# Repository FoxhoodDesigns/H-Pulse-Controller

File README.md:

# H-Pulse Train controller (G4)
A advanced Electronic Speed Control intended for controlling Model trains. Though the load is simple, this ESC is equipped with the means to enable advanced monitoring/control of model trains
In the long-run the controller can be programmed to be able to communicate to digital trains via Digital-Command-Control (DCC)

# Specifications:
+ INPUT:	8-24V DC
+ OUTPUT: 8-24V <6A
+ TDP: ~1-5 Watt depending on load
+ Controller: Raspberry Pi RP2040 125Mhz Dual-core ARM microcontroller.
+ Driver: Infineon TLE9201 6A H-Bridge motor driver with SPI interface
+ Display: GC9A01 240x240 circular IPS Monitor

# Features:
+ Current Monitoring
+ Voltage Monitoring
+ Reverse Polarity Protection
+ Transient Voltage Suppression
+ Overcurrent Detection / Short-circuit protection
+ Under-voltage lockout
+ Open-load (Derail) detection
+ FAN Load switch
+ Piezo-speaker for feedback
+ Extra headers for (Matrix) IO
+ DCC-Ready Hardware

# Current Status:
Testing IO Expansion part on a breadboard. Creating initial firmware and drawing the Icons that are to be displayed on the GC9A01.

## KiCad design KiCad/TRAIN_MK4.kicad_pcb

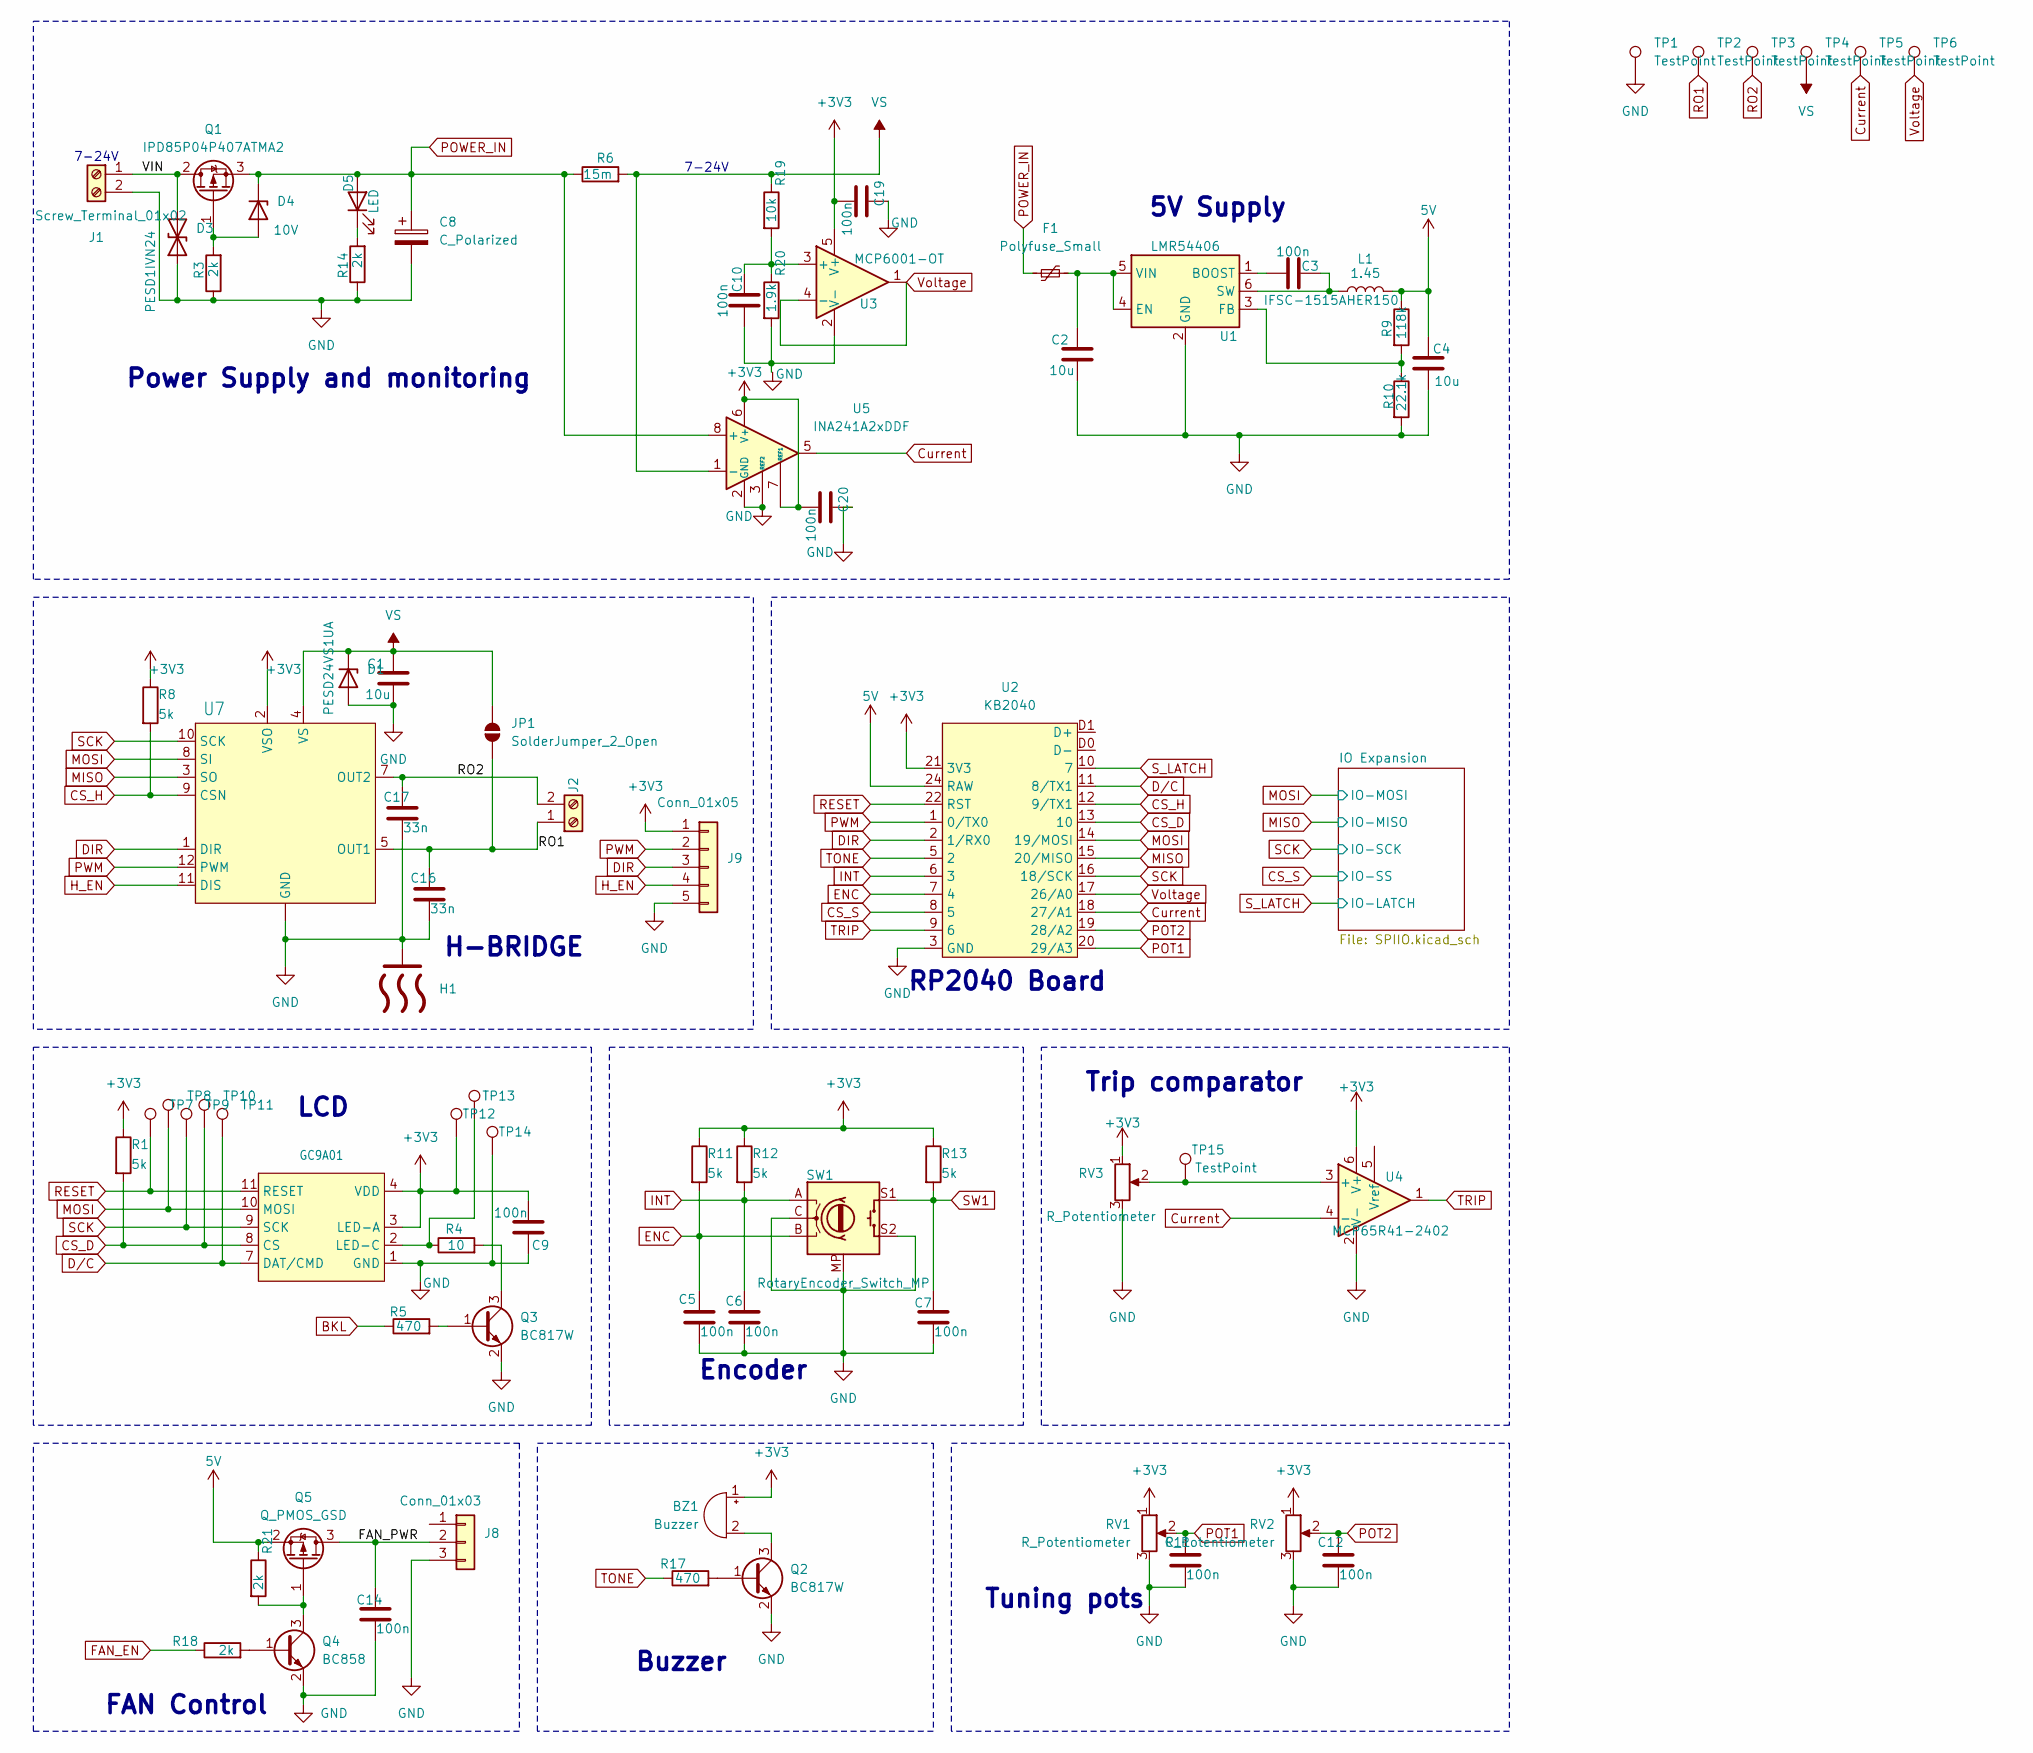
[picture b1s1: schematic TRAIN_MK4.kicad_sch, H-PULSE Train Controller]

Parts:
BZ1: Buzzer; PUIAudio_SMT_0825_S_4_R
C1, C2, C4: 10u; C_1210_3225Metric_Pad1.33x2.70mm_HandSolder
C3, C5, C6, C7, C9, C10, C11, C12, C14, C19, C20: 100n; C_0805_2012Metric_Pad1.18x1.45mm_HandSolder; Voltage 1kV; Tolerance 100%
C8: C_Polarized; CP_Elec_10x10
C16, C17: 33n; C_0805_2012Metric_Pad1.18x1.45mm_HandSolder; Voltage 1kV; Tolerance 100%
D1: PESD24VS1UA; D_SOD-323_HandSoldering
D3: PESD1IVN24; D_SOD-323_HandSoldering
D4: 10V; Nexperia_CFP3_SOD-123W
D5: LED; LED_0805_2012Metric_Pad1.15x1.40mm_HandSolder
F1: Polyfuse_Small; Fuse_1812_4532Metric_Pad1.30x3.40mm_HandSolder
H1: DPAK-Heatsink
J1, J2: Screw_Terminal_01x02; TerminalBlock_Phoenix_PT-1,5-2-5.0-H_1x02_P5.00mm_Horizontal
J8: Conn_01x03; FanPinHeader_1x03_P2.54mm_Vertical
J9: Conn_01x05; PinHeader_1x05_P2.54mm_Vertical
JP1: SolderJumper_2_Open; SolderJumper-2_P1.3mm_Open_Pad1.0x1.5mm
L1: IFSC-1515AHER150; L_Vishay_IFSC-1515AH_4x4x1.8mm
Q1: IPD85P04P407ATMA2; TO-252-2
Q2, Q3: BC817W; SOT-323_SC-70
Q4: BC858; SOT-323_SC-70_Handsoldering
Q5: Q_PMOS_GSD; SOT-23
R1, R8, R11, R12, R13: 5k; R_0805_2012Metric_Pad1.20x1.40mm_HandSolder
R3, R14, R18, R21: 2k; R_0805_2012Metric_Pad1.20x1.40mm_HandSolder
R4: 10; R_0805_2012Metric_Pad1.20x1.40mm_HandSolder
R5, R17: 470; R_0805_2012Metric_Pad1.20x1.40mm_HandSolder
R6: 15m; R_2010_5025Metric_Pad1.40x2.65mm_HandSolder
R9: 118k; R_0805_2012Metric_Pad1.20x1.40mm_HandSolder
R10: 22.1k; R_0805_2012Metric_Pad1.20x1.40mm_HandSolder
R19: 10k; R_0805_2012Metric_Pad1.20x1.40mm_HandSolder
R20: 1.9k; R_0805_2012Metric_Pad1.20x1.40mm_HandSolder
RV1, RV2: R_Potentiometer; Potentiometer_Vishay_T73YP_Vertical
RV3: R_Potentiometer; Potentiometer_Bourns_3214X_Vertical
SW1: RotaryEncoder_Switch_MP; RotaryEncoder_Bourns_Vertical_PEC12R-3x17F-Sxxxx
TP1, TP2, TP3, TP4, TP5, TP6: TestPoint; TestPoint_Pad_2.0x2.0mm
TP7, TP8, TP9, TP10, TP11, TP12, TP13, TP14: TestPoint; TestPoint_Pad_D1.0mm
TP15: TestPoint; TestPoint_Pad_D2.0mm
U1: LMR54406; TSOT-23-6
U2: KB2040
U3: MCP6001-OT; SOT-23-5
U4: MCP65R41-2402; SOT-23-6
U5: INA241A2xDDF; SOT-23-8
U7: Infineon_PG-DSO-12-17
U8: GC9A01; GC9A01INT

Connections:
5V: C4.1, L1.2, Q5.2 (S), R9.1, R21.1, U2.24 (RAW)
+3V3: BZ1.1 (+), C9.2, C19.2, C20.2, J9.1, R1.1, R8.1, R11.1, R12.1, R13.1, RV1.1, RV2.1, RV3.1, TP12.1, U2.21 (3V3), U3.5 (V+), U4.6 (V+), U5.6 (V+), U5.7 (REF1), U7.2 (VSO), U8.3 (LED-A), U8.4 (VDD); also elsewhere on the board
/FAN_PWR: C14.1, J8.2, Q5.3 (D)
/VIN: D3.2 (A2), J1.1, Q1.2 (D)
BKL: R5.1; also elsewhere on the board
CS_D: R1.2, TP10.1, U2.13 (10), U8.8 (CS)
CS_H: R8.2, U2.12 (9/TX1), U7.9 (CSN)
CS_S: U2.8 (5); also elsewhere on the board
Current: TP5.1, U2.18 (27/A1), U4.4 (-), U5.5
DIR: J9.3, U2.2 (1/RX0), U7.1 (DIR)
D/C: TP11.1, U2.11 (8/TX1), U8.7 (DAT/CMD)
ENC: C5.1, R11.2, SW1.B, U2.7 (4)
FAN_EN: R18.1; also elsewhere on the board
GND: C1.2, C2.2, C4.2, C5.2, C6.2, C7.2, C8.2, C9.1, C11.2, C12.2, C14.2, C16.2, C17.2, C19.1, C20.1, D1.2 (A), D3.1 (A1), H1.1, J1.2, J8.3, J9.5, Q2.2 (E), Q3.2 (E), Q4.2 (E), R3.1, R10.2, R14.1, RV1.3, RV2.3, RV3.3, SW1.C, SW1.MP, SW1.S2, TP1.1, TP14.1, U1.2 (GND), U2.3 (GND), U2.4 (GND), U2.23 (GND), U4.2 (V-), U5.2 (GND), U5.3 (REF2), U5.4 (GND), U7.6 (GND), U7.13 (GND), U8.1 (GND), U8.5 (GND), U8.6 (GND), U8.12 (GND); also elsewhere on the board
H_EN: J9.4, U7.11 (DIS); also elsewhere on the board
INT: C6.1, R12.2, SW1.A, U2.6 (3)
MISO: U2.15 (20/MISO), U7.3 (SO); also elsewhere on the board
MOSI: TP8.1, U2.14 (19/MOSI), U7.8 (SI), U8.10 (MOSI); also elsewhere on the board
unnamed: BZ1.2 (-), Q2.3 (C)
unnamed: D4.2 (A), Q1.1 (G), R3.2
unnamed: D5.1 (K), R14.2
unnamed: Q2.1 (B), R17.2
unnamed: Q3.1 (B), R5.2
unnamed: Q3.3 (C), R4.2
unnamed: Q4.1 (B), R18.2
unnamed: Q4.3 (C), Q5.1 (G), R21.2
unnamed: C3.2, U1.1 (BOOST)
unnamed: C2.1, F1.2, U1.4 (EN), U1.5 (VIN)
unnamed: R9.2, R10.1, U1.3 (FB)
unnamed: C3.1, L1.1, U1.6 (SW)
unnamed: C10.1, R19.2, R20.1, U3.3 (+)
unnamed: C10.2, R20.2, U3.2 (V-)
unnamed: RV3.2, TP15.1, U4.3 (+)
unnamed: R4.1, TP13.1, U8.2 (LED-C)
POT1: C11.1, RV1.2, U2.20 (29/A3)
POT2: C12.1, RV2.2, U2.19 (28/A2)
POWER_IN: C8.1, D4.1 (K), D5.2 (A), F1.1, Q1.3 (S), R6.1, U5.8 (+)
PWM: J9.2, U2.1 (0/TX0), U7.12 (PWM)
RESET: TP7.1, U2.22 (RST), U8.11 (RESET)
RO1: C16.1, J2.1, JP1.1 (A), TP2.1, U7.5 (OUT1)
RO2: C17.1, J2.2, TP3.1, U7.7 (OUT2)
SCK: TP9.1, U2.16 (18/SCK), U7.10 (SCK), U8.9 (SCK); also elsewhere on the board
SW1: C7.1, R13.2, SW1.S1; also elsewhere on the board
S_LATCH: U2.10 (7); also elsewhere on the board
TONE: R17.1, U2.5 (2)
TRIP: U2.9 (6), U4.1
VS: C1.1, D1.1 (K), JP1.2 (B), R6.2, R19.1, TP4.1, U5.1 (-), U7.4 (VS)
Voltage: TP6.1, U2.17 (26/A0), U3.1, U3.4 (-)

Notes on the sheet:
H-BRIDGE
Tuning pots
LCD
7-24V
Buzzer
RP2040 Board
5V Supply
FAN Control
Power Supply and monitoring
Trip comparator
Encoder

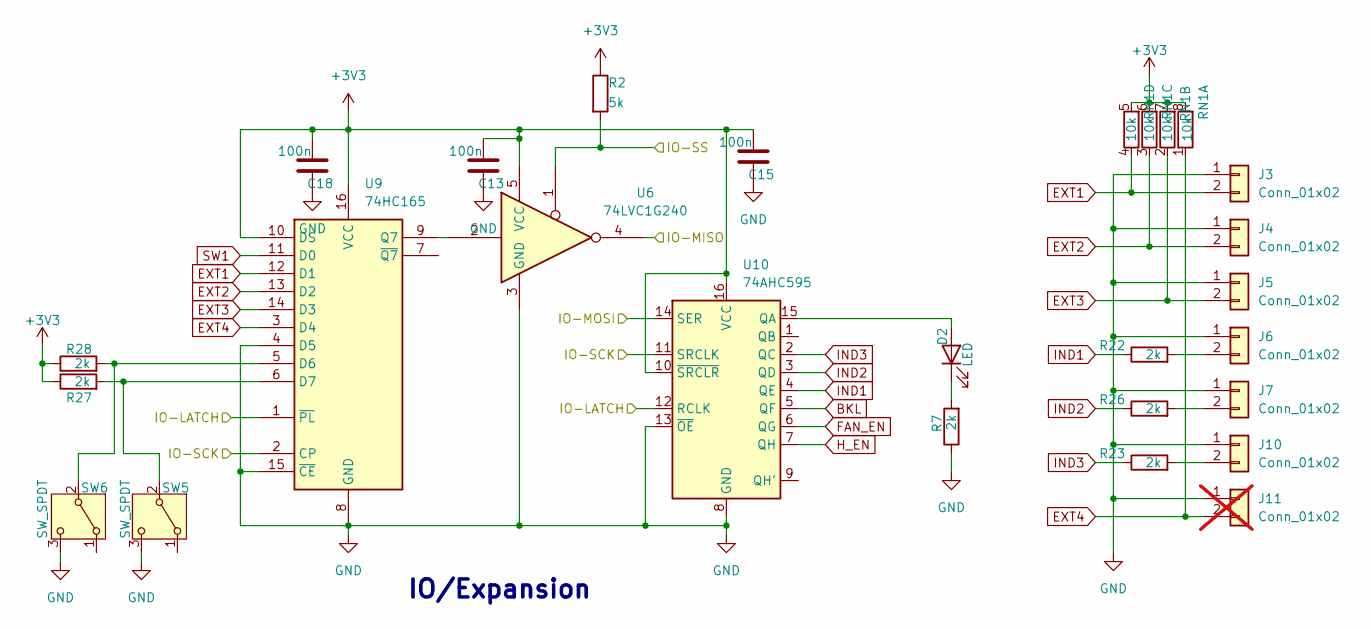
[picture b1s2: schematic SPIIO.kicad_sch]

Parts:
C13, C15, C18: 100n; C_0805_2012Metric_Pad1.18x1.45mm_HandSolder; Voltage 1kV; Tolerance 100%
D2: LED; LED_0805_2012Metric_Pad1.15x1.40mm_HandSolder
J3, J4, J5, J6, J7, J10: Conn_01x02; JST_XH_B2B-XH-A_1x02_P2.50mm_Vertical
J11: Conn_01x02; PinHeader_1x02_P2.54mm_Vertical_SMD_Pin1Right; not fitted
R2: 5k; R_0805_2012Metric_Pad1.20x1.40mm_HandSolder
R7, R22, R23, R26, R27, R28: 2k; R_0805_2012Metric_Pad1.20x1.40mm_HandSolder
RN1: 10k; R_Array_Convex_4x0603
SW5, SW6: SW_SPDT; SW_Slide_SPDT_Straight_CK_OS102011MS2Q
U6: 74LVC1G240; SOT-23-5_HandSoldering
U9: 74HC165; TSSOP-16_4.4x5mm_P0.65mm
U10: 74AHC595; TSSOP-16_4.4x5mm_P0.65mm

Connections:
+3V3: C13.2, C15.2, C18.2, R2.1, R27.1, R28.1, RN1.5 (R4.2), RN1.6 (R3.2), RN1.7 (R2.2), RN1.8 (R1.2), U6.5 (VCC), U9.10 (DS), U9.16 (VCC), U10.10 (~SRCLR), U10.16 (VCC); also elsewhere on the board
BKL: U10.5 (QF); also elsewhere on the board
CS_S: R2.2, U6.1; also elsewhere on the board
EXT1: J3.2, RN1.4 (R4.1), U9.12 (D1)
EXT2: J4.2, RN1.3 (R3.1), U9.13 (D2)
EXT3: J5.2, RN1.2 (R2.1), U9.14 (D3)
EXT4: J11.2, RN1.1 (R1.1), U9.3 (D4)
FAN_EN: U10.6 (QG); also elsewhere on the board
GND: C13.1, C15.1, C18.1, J3.1, J4.1, J5.1, J6.1, J7.1, J10.1, J11.1, R7.1, SW5.3 (C), SW6.3 (C), U6.3 (GND), U9.4 (D5), U9.8 (GND), U9.15 (~CE), U10.8 (GND), U10.13 (~OE); also elsewhere on the board
H_EN: U10.7 (QH); also elsewhere on the board
IND1: R22.1, U10.4 (QE)
IND2: R26.1, U10.3 (QD)
IND3: R23.1, U10.2 (QC)
MISO: U6.4; also elsewhere on the board
MOSI: U10.14 (SER); also elsewhere on the board
unnamed: D2.2 (A), U10.15 (QA)
unnamed: D2.1 (K), R7.2
unnamed: J6.2, R22.2
unnamed: J7.2, R26.2
unnamed: J10.2, R23.2
unnamed: R27.2, SW5.2 (B), U9.6 (D7)
unnamed: R28.2, SW6.2 (B), U9.5 (D6)
unnamed: U6.2, U9.9 (Q7)
SCK: U9.2 (CP), U10.11 (SRCLK); also elsewhere on the board
SW1: U9.11 (D0); also elsewhere on the board
S_LATCH: U9.1 (~PL), U10.12 (RCLK); also elsewhere on the board

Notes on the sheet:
IO/Expansion

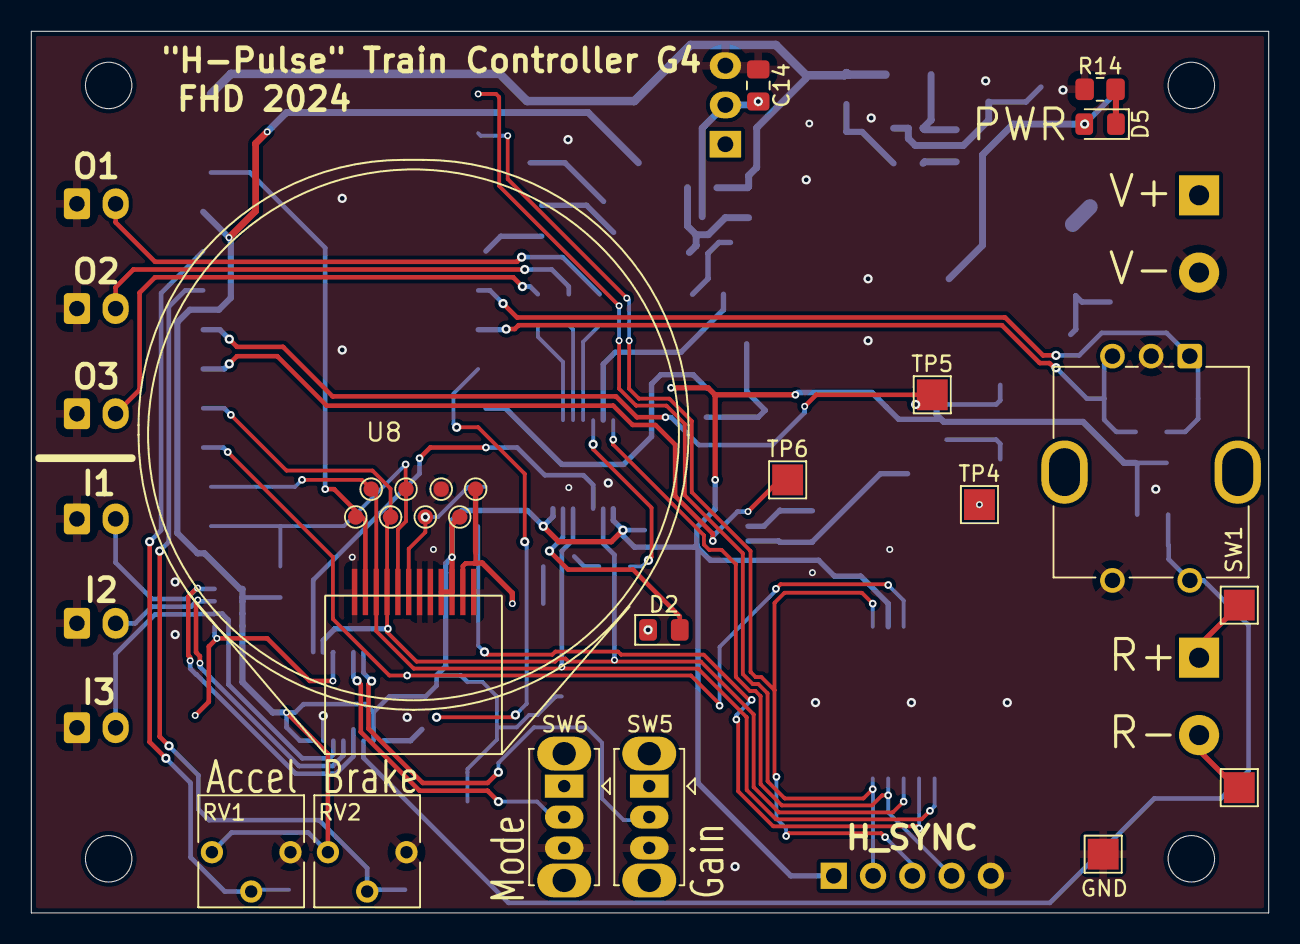
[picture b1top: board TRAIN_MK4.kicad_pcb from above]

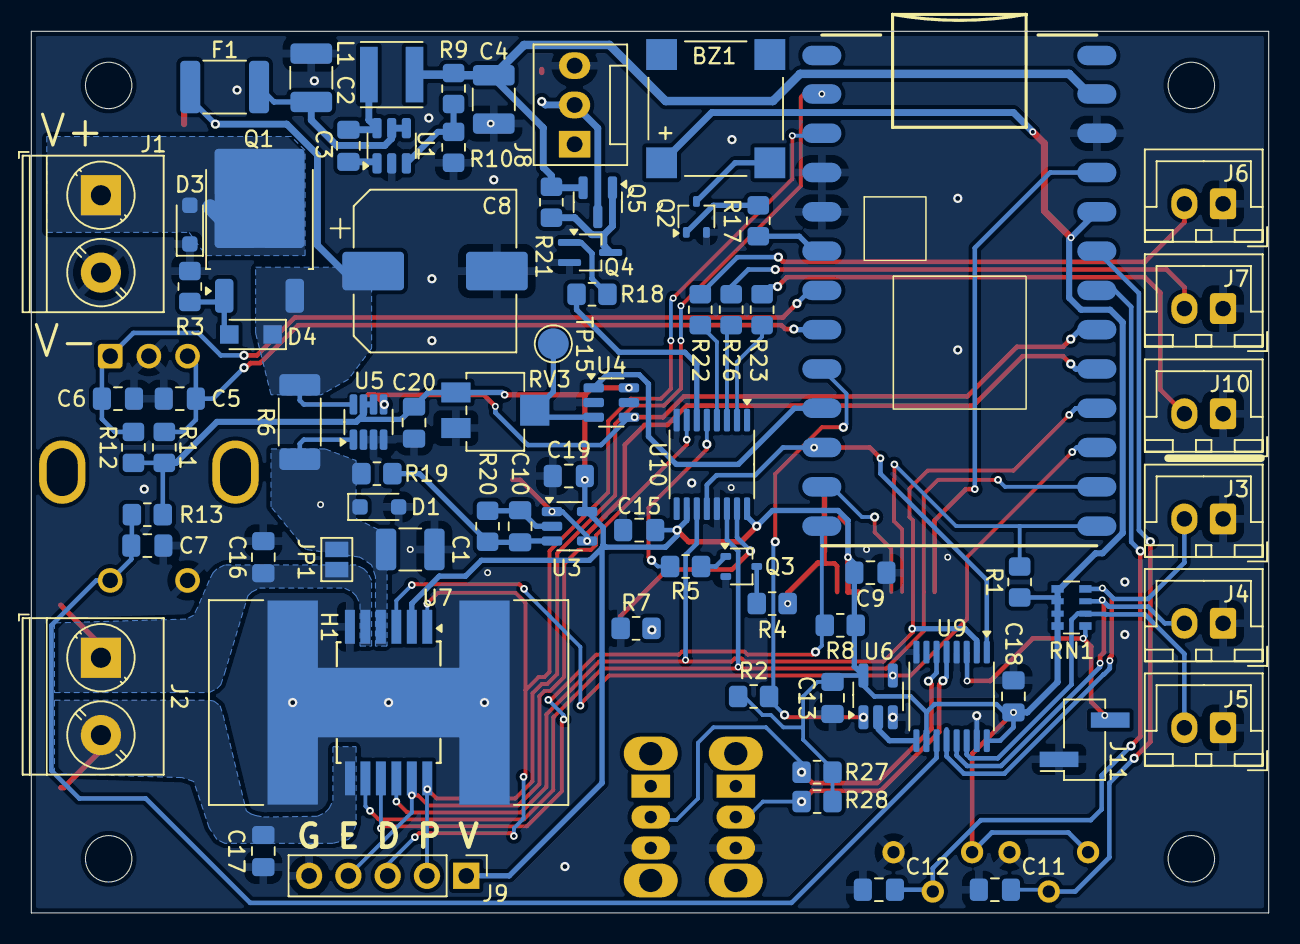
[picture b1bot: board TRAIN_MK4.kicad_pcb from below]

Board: 2 copper layers, 80.0 x 57.0 mm, 102 parts (78 on the bottom side), 63 nets.

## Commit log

2025-02-23 Initial Upload
    Initial Upload of Schematic and PCB
2025-02-24 Update
    Dividing schematic part 1
2025-02-24 Update
    Documentation related changes and small DRU corrections
